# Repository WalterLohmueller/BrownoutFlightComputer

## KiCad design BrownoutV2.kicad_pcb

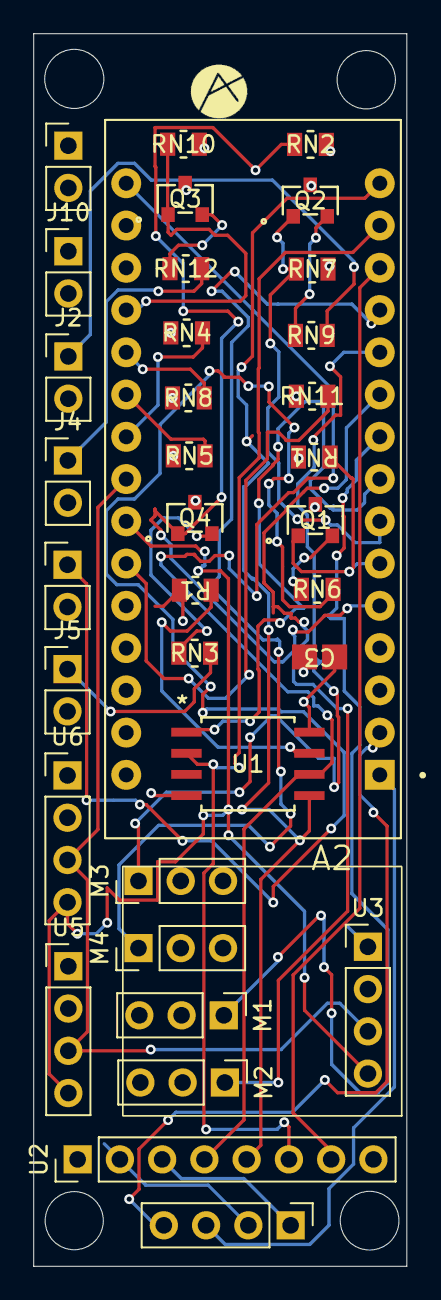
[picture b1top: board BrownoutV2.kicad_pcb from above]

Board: 4 copper layers, 22.4 x 74.1 mm, 34 parts (0 on the bottom side), 32 nets.

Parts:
A2: Arduino_Nano_Every; Arduino_nano_33_iot
C3: 22pf; 22pfcap
J1, J2, J3, J4, J5, J10: Screw_Terminal_01x02; PinHeader_1x02_P2.54mm_Vertical
M1, M2, M3, M4: Motor_Servo_JR; servo
Q1, Q2, Q3, Q4: NTR2101P; smdnchanelmsofet
R1: 10M; SMDresistor
RN1, RN2, RN7, RN10: 470ohm; SMDresistor
RN3, RN6, RN9, RN12: 1 OHM; SMDresistor
RN4, RN5, RN8, RN11: 100KOHM; SMDresistor
U1: W25Q128JVSIQ; flash
U2: PinHeader_1x08_P2.54mm_Vertical
U3, U5, U6: PinHeader_1x04_P2.54mm_Vertical

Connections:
+3.3V: A2.17 (3V3), C3.1, R1.2, U1.8 (VCC), U2.2 (3V), U3.1 (3.3V), U5.1 (3.3V), U6.1 (3.3V)
/A0: A2.19 (A0), Q3.1 (G), RN10.1 (R1)
/A1: A2.20 (A1), RN8.2 (R1.2)
/A2: A2.21 (A2), RN5.2 (R1.2)
/A3: A2.22 (A3), RN4.2 (R1.2)
/A6: A2.25 (A6), RN11.2 (R1.2)
/BATT+: J1.2, J2.2, J4.2, J5.2, J10.2, M1.2 (+), M2.2 (+), M3.2 (+), M4.2 (+)
/D2: A2.5 (D2), Q4.1 (G), RN2.1 (R1)
/D3: A2.6 (D3), Q1.1 (G), RN1.1 (R1)
/D4: A2.7 (D4), Q2.1 (G), RN7.1 (R1)
/FLASH_CS: A2.8 (D5), U1.1 (/CS)
/MISO: A2.15 (MISO), U1.5 (DI_(IO0)), U2.5 (D0)
/MOSI: A2.14 (MOSI), U1.2 (DO_(IO1)), U2.6 (D1)
/SCK: A2.16 (SCK), U1.6 (CLK), U2.4 (CLK)
/SCL: A2.24 (SCL/A5), U3.4 (SCL), U5.4, U6.4
/SDA: A2.23 (SDA/A4), U3.3 (SDA), U5.3 (SDA), U6.3 (SDA)
/SD_CS: A2.13 (D10), U2.7 (CS)
/SERVO1: A2.9 (D6), M1.1 (PWM)
/SERVO2: A2.10 (D7), M2.1 (PWM)
/SERVO3: A2.11 (D8), M3.1 (PWM)
/SERVO4: A2.12 (D9), M4.1 (PWM)
BATT: A2.30 (VIN), J3.2, J10.1, RN4.1 (R1), RN5.1 (R1), RN8.1 (R1), RN11.1 (R1)
GND: A2.4 (GND), A2.29 (GND), C3.2, J3.1, M1.3 (-), M2.3 (-), M3.3 (-), M4.3 (-), Q1.3 (D), Q2.3 (D), Q3.3 (D), Q4.3 (D), RN1.2 (R1.2), RN2.2 (R1.2), RN7.2 (R1.2), RN10.2 (R1.2), U1.4 (GND), U2.3 (GND), U3.2 (GND), U5.2, U6.2
unnamed: J1.1, RN6.2 (R1.2)
unnamed: J2.1, RN9.2 (R1.2)
unnamed: J4.1, RN12.2 (R1.2)
unnamed: J5.1, RN3.2 (R1.2)
unnamed: Q1.2 (S), RN6.1 (R1)
unnamed: Q2.2 (S), RN9.1 (R1)
unnamed: Q3.2 (S), RN12.1 (R1)
unnamed: Q4.2 (S), RN3.1 (R1)
unnamed: R1.1, U1.7 (/HOLD_or_/RESET_(IO3))

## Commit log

2023-10-06 Create Code
